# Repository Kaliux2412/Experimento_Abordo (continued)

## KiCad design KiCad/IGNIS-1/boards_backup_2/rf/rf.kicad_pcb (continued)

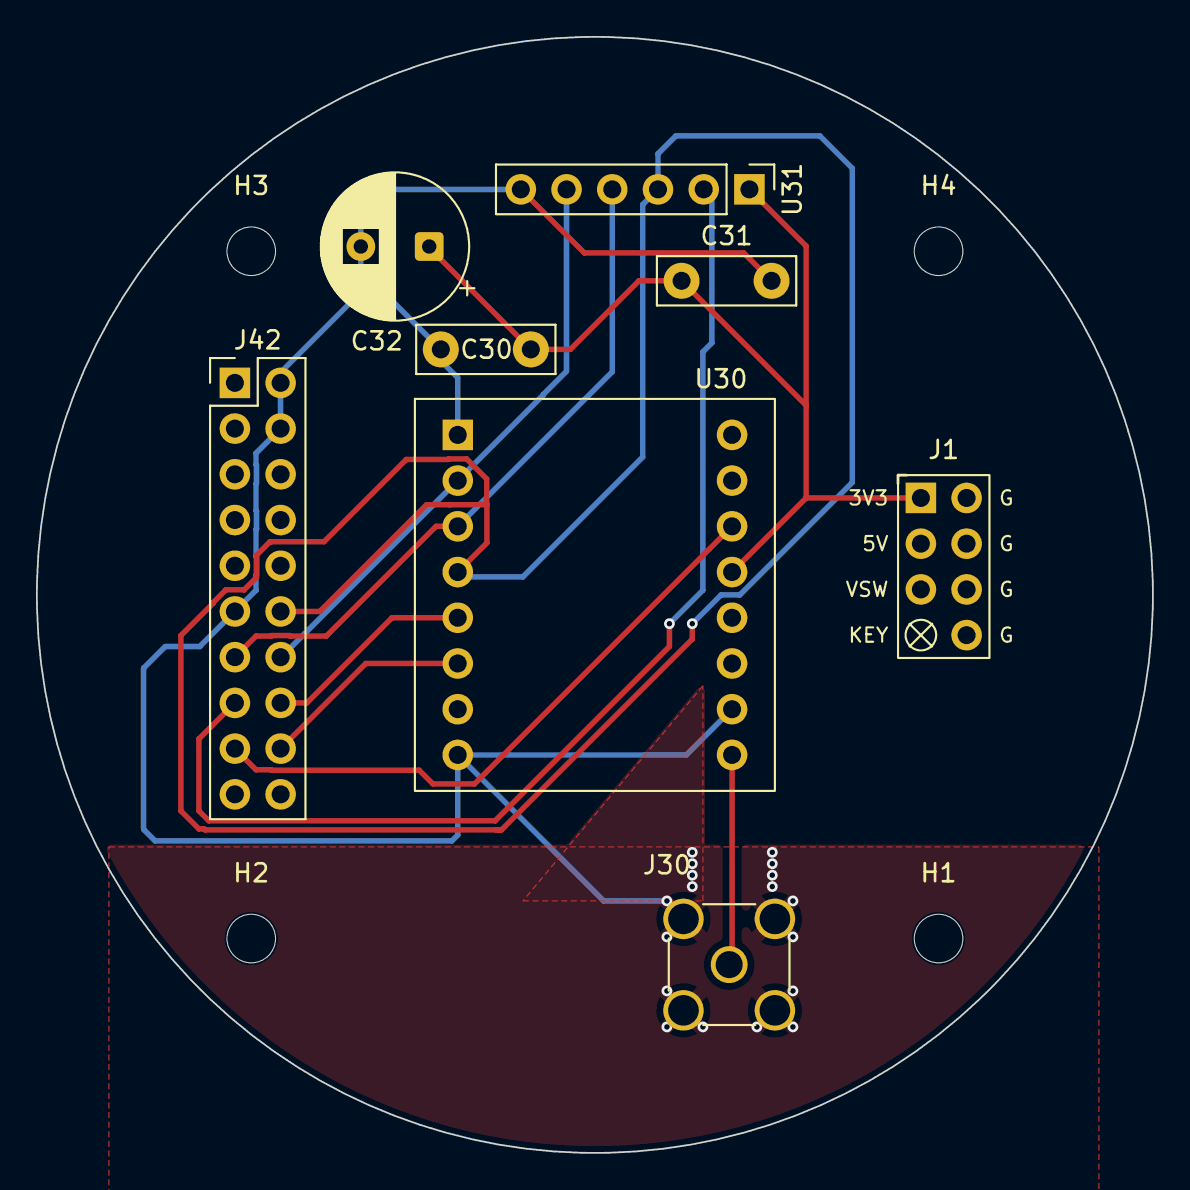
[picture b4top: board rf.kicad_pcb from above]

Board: 2 copper layers, 62.0 x 62.0 mm, 12 parts (0 on the bottom side), 10 nets.

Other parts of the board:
H1, H2, H3, H4: M2.5_hole; MountingHole_2.7mm_M2.5

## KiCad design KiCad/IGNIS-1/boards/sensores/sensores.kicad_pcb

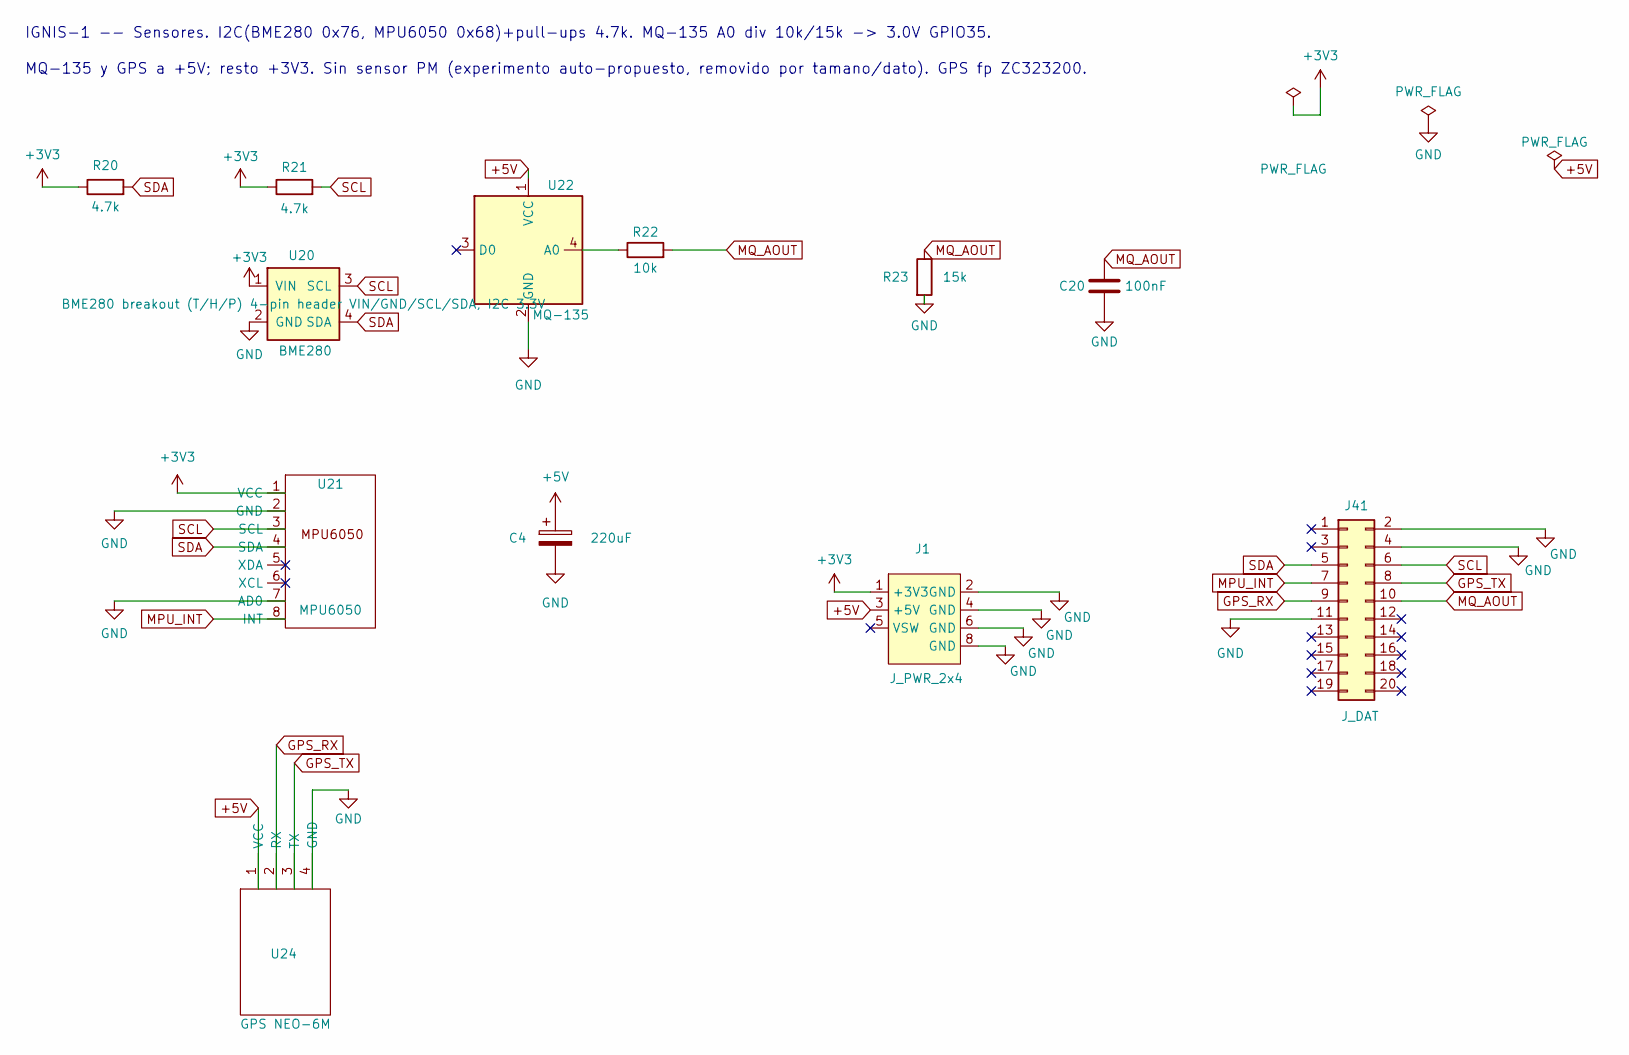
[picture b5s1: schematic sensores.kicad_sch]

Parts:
C4: 220uF; CP_Radial_D13.0mm_P5.00mm
C20: 100nF; C_Disc_D7.5mm_W2.5mm_P5.00mm
J1: J_PWR_2x4; J_PWR_2x4_Keyed
J41: J_DAT; PinHeader_2x10_P2.54mm_Vertical
R20, R21: 4.7k; R_Axial_DIN0207_L6.3mm_D2.5mm_P7.62mm_Horizontal
R22: 10k; R_Axial_DIN0207_L6.3mm_D2.5mm_P7.62mm_Horizontal
R23: 15k; R_Axial_DIN0207_L6.3mm_D2.5mm_P7.62mm_Horizontal
U20: BME280; PinHeader_1x04_P2.54mm_Vertical
U21: MPU6050; MPU6050_module
U22: MQ-135; PinHeader_1x04_P2.54mm_Vertical
U24: GPS NEO-6M; GPS_NEO6M_module

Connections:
+3V3: J1.1 (+3V3), R20.1, R21.1, U20.1 (VIN), U21.1 (VCC)
+5V: C4.1, J1.3 (+5V), U22.1 (VCC), U24.1 (VCC)
GND: C4.2, C20.2, J1.2 (GND), J1.4 (GND), J1.6 (GND), J1.8 (GND), J41.2, J41.4, J41.11, R23.2, U20.2 (GND), U21.2 (GND), U21.7 (AD0), U22.2 (GND), U24.4 (GND)
GPS_RX: J41.9, U24.2 (RX)
GPS_TX: J41.8, U24.3 (TX)
MPU_INT: J41.7, U21.8 (INT)
MQ_AOUT: C20.1, J41.10, R22.2, R23.1
unnamed: R22.1, U22.4 (A0)
SCL: J41.6, R21.2, U20.3 (SCL), U21.3 (SCL)
SDA: J41.5, R20.2, U20.4 (SDA), U21.4 (SDA)

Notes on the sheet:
IGNIS-1 -- Sensores. I2C(BME280 0x76, MPU6050 0x68)+pull-ups 4.7k. MQ-135 A0 div 10k/15k -> 3.0V GPIO35.
MQ-135 y GPS a +5V; resto +3V3. Sin sensor PM (experimento auto-propuesto, removido por tamano/dato). GPS fp ZC323200.

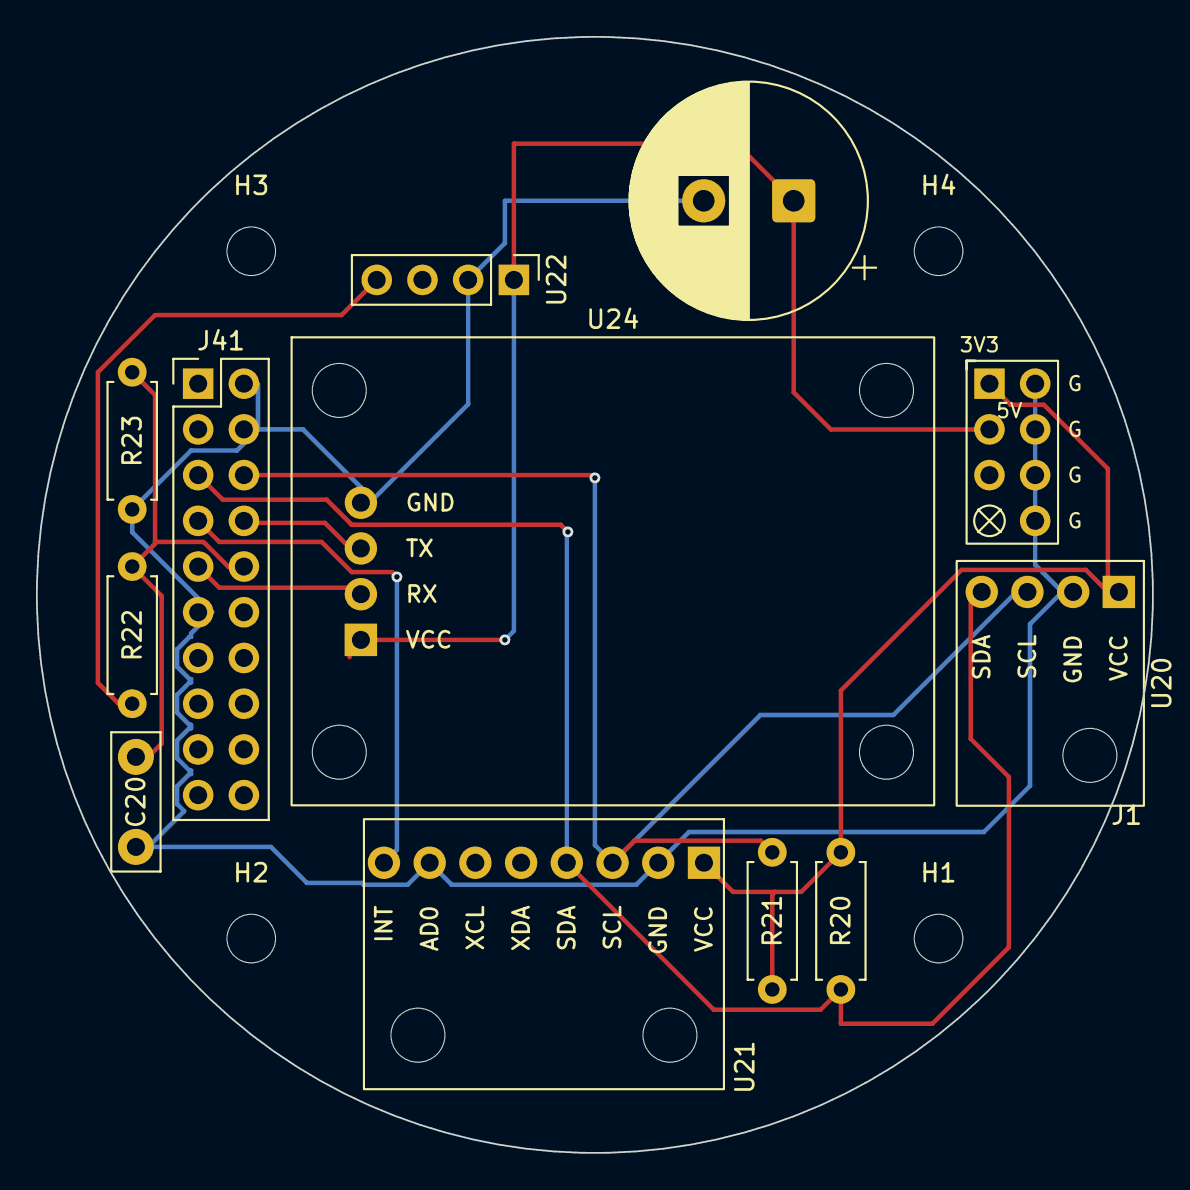
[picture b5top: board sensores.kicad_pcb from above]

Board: 2 copper layers, 62.0 x 62.0 mm, 16 parts (0 on the bottom side), 10 nets.

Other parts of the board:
H1, H2, H3, H4: M2.5_hole; MountingHole_2.7mm_M2.5

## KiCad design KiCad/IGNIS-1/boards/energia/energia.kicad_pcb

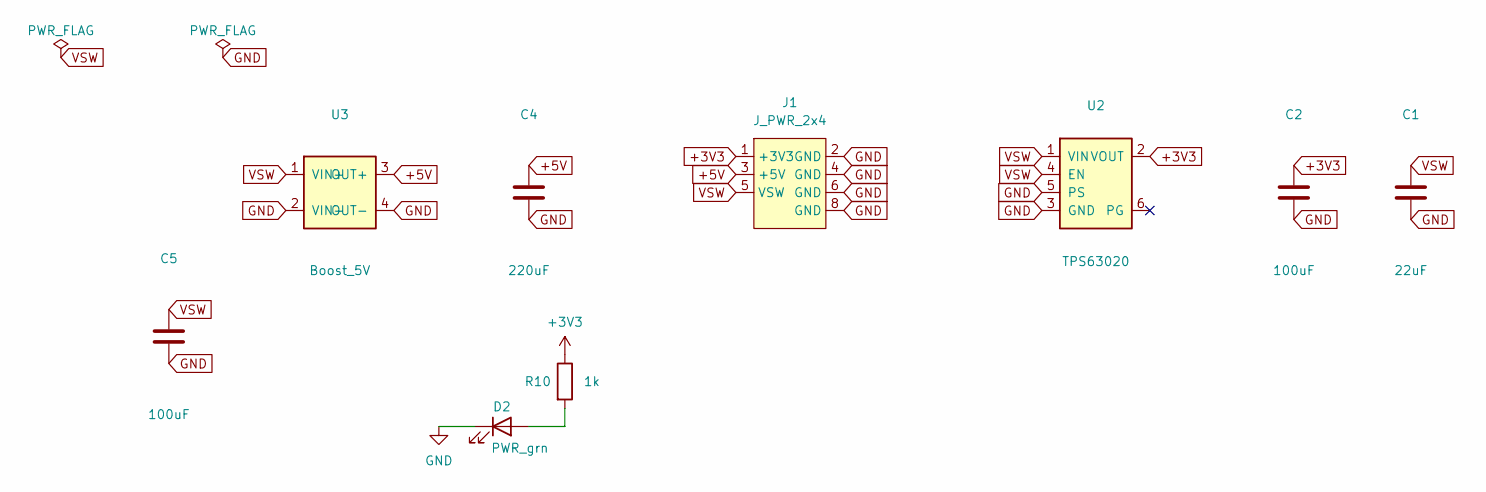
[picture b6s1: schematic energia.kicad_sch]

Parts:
C1: 22uF; CP_Radial_D6.3mm_P2.50mm
C2, C5: 100uF; CP_Radial_D8.0mm_P3.80mm
C4: 220uF; CP_Radial_D13.0mm_P5.00mm
D2: PWR_grn; LED_D3.0mm
J1: J_PWR_2x4; J_PWR_2x4_Keyed
R10: 1k; R_Axial_DIN0207_L6.3mm_D2.5mm_P7.62mm_Horizontal
U2: TPS63020; TPS63020_module
U3: Boost_5V; MT3608_module

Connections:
+3V3: C2.1, J1.1 (+3V3), R10.1, U2.2 (VOUT)
+5V: C4.1, J1.3 (+5V), U3.3 (OUT+)
GND: C1.2, C2.2, C4.2, C5.2, D2.1 (K), J1.2 (GND), J1.4 (GND), J1.6 (GND), J1.8 (GND), U2.3 (GND), U2.5 (PS), U3.2 (VIN-), U3.4 (OUT-)
unnamed: D2.2 (A), R10.2
VSW: C1.1, C5.1, J1.5 (VSW), U2.1 (VIN), U2.4 (EN), U3.1 (VIN+)

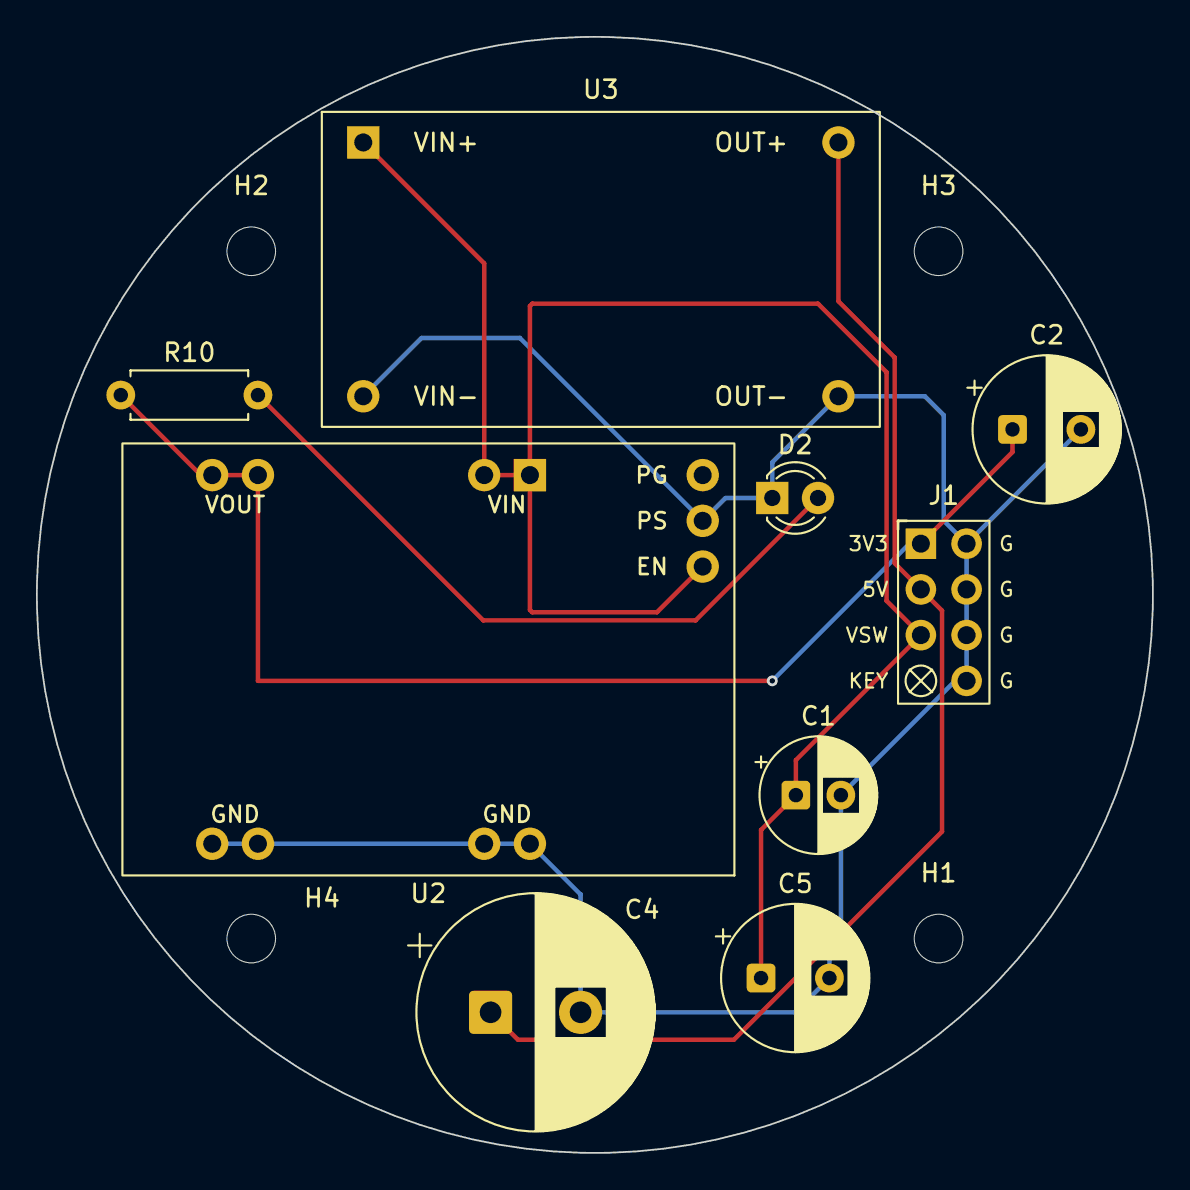
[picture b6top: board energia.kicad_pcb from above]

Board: 2 copper layers, 62.0 x 62.0 mm, 13 parts (0 on the bottom side), 5 nets.

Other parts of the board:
H1, H2, H3, H4: M2.5_hole; MountingHole_2.7mm_M2.5

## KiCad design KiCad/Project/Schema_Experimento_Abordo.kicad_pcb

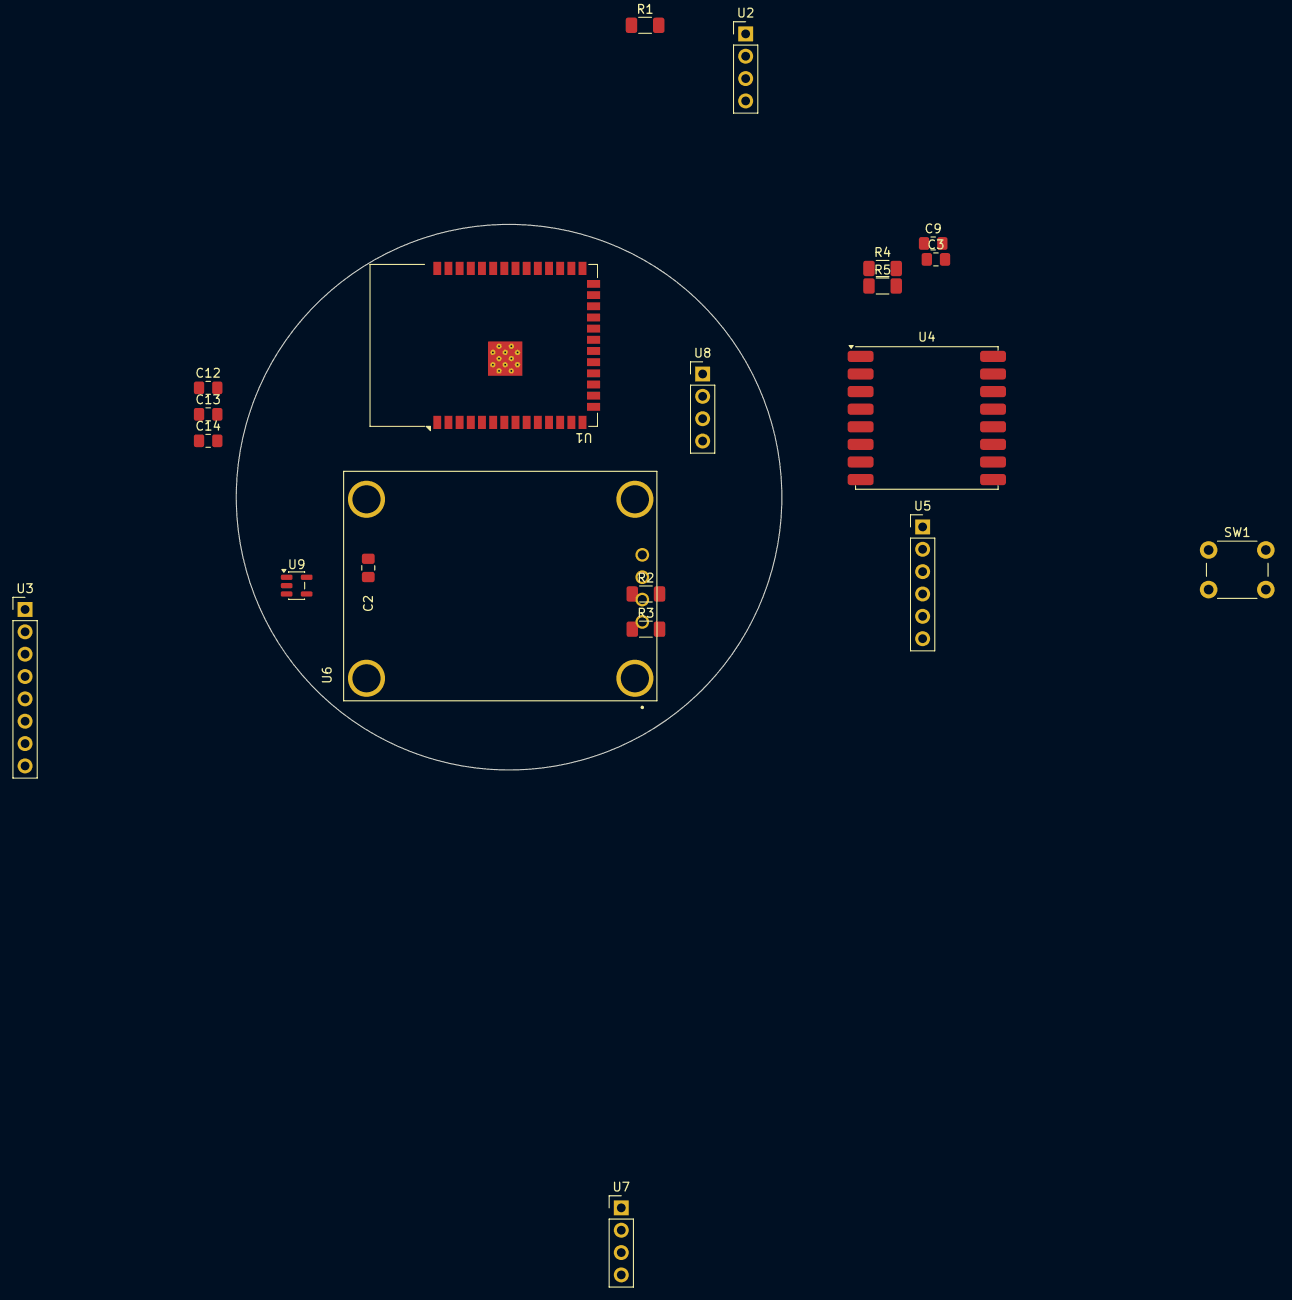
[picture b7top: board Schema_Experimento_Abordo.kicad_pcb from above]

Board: 2 copper layers, 62.0 x 62.0 mm, 21 parts (0 on the bottom side), 17 nets, no tracks yet.

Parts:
C2, C9, C12, C13: 10uF; C_0805_2012Metric_Pad1.18x1.45mm_HandSolder
C3: 0.1uF; C_0805_2012Metric_Pad1.18x1.45mm_HandSolder
C14: 100nF; C_0805_2012Metric_Pad1.18x1.45mm_HandSolder
R1: 10k; R_1206_3216Metric_Pad1.30x1.75mm_HandSolder
R2, R3: 4.7k; R_1206_3216Metric_Pad1.30x1.75mm_HandSolder
R4, R5: 100k; R_1206_3216Metric_Pad1.30x1.75mm_HandSolder
SW1: RESET; SW_PUSH_6mm_H4.3mm
U1: ESP32-S3-WROOM-1
U2: BME280; PinHeader_1x04_P2.54mm_Vertical
U3: PinHeader_1x08_P2.54mm_Vertical
U4: HOPERF_RFM9XW_SMD
U5: Micro_SD; PinHeader_1x06_P2.54mm_Vertical
U6: ZC323200; XCVR_ZC323200
U7: SGP30; PinHeader_1x04_P2.54mm_Vertical
U8: PinHeader_1x04_P2.54mm_Vertical
U9: AP2112K-3.3; SOT-23-5

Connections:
+3.3V: C2.1, C9.1, C13.1, C14.1, R1.2, R2.2, R3.2, U1.1 (3V3), U1.16 (VIN), U2.1 (VIN), U3.1 (VCC), U4.12 (3.3V), U5.1 (VCC), U6.1 (VCC), U7.1 (VIN), U8.1 (VIN), U9.5 (VOUT)
+BATT: C12.1, R5.1, U9.1 (VIN), U9.3 (EN)
/CS MicroSD: U1.18 (D13), U5.2 (CS)
/DIO0 LoRa: U1.22 (D26), U4.11 (DIO0)
/GPS_RX: U1.7 (TX2), U6.2 (RX)
/GPS_TX: U1.6 (RX2), U6.3 (TX)
/MISO SPI: U1.10 (D19), U4.2 (MISO), U5.5 (MISO)
/MOSI SPI: U1.15 (D23), U4.3 (MOSI), U5.3 (MOSI)
/MPU6050 INT: U1.21 (D27), U3.8 (INT)
/NSS LoRa: U1.8 (D5), U4.5 (NSS)
/RST LoRa: U1.20 (D14), U4.6 (RESET)
/SCK SPI: U1.9 (D18), U4.4 (SCK), U5.4 (CLK)
/SCL: R3.1, U1.25 (D32), U2.3 (SCL), U3.3 (SCL), U7.3 (SCL), U8.3 (SCL)
/SDA: R2.1, U1.24 (D33), U2.4 (SDA), U3.4 (SDA), U7.4 (SDA), U8.4 (SDA)
GND: C2.2, C3.2, C9.2, C12.2, C13.2, C14.2, R4.1, SW1.1, U1.2 (GND), U1.17 (GND), U1.40 (GND), U1.41 (GND), U2.2 (GND), U3.2 (GND), U3.7 (AD0), U4.1 (GND), U5.6 (GND), U6.4 (GND), U6.SH1 (GND), U6.SH2 (GND), U6.SH3 (GND), U6.SH4 (GND), U7.2 (GND), U8.2 (GND), U9.2 (GND)
unnamed: R4.2, R5.2, U1.27 (D34)
unnamed: C3.1, R1.1, SW1.2, U1.30 (EN)

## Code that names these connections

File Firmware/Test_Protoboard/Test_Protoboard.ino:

/*
 * IGNIS-1 — Test de protoboard (bring-up de hardware)
 * --------------------------------------------------------------
 * NO es el firmware de vuelo. Solo verifica que cada periferico
 * responde, con el pin-map del diseno. Cada subsistema imprime
 * PASS/FAIL y se puede desactivar si el modulo no esta conectado.
 *
 * Pin-map (ESP32 DevKit 38p):
 *   I2C  SDA/SCL ......... 33 / 32   (BME280 0x76, MPU6050 0x68)
 *   SPI  SCK/MISO/MOSI ... 18 / 19 / 23   (LoRa + microSD, CS separados)
 *   LoRa CS/RST/DIO0 ..... 5 / 14 / 26   (RFM95W 433 MHz)
 *   microSD CS ........... 13
 *   MPU_INT .............. 27
 *   Buzzer ............... 25   (activo)
 *   LED status ........... 4
 *   GPS  RX2/TX2 ......... 16 / 17   (NEO-6M, 9600 baud)
 *   MQ-135 A0 ............ 35   (ADC1, via divisor 10k/15k)
 *
 * Librerias (Library Manager):
 *   Adafruit BME280, Adafruit MPU6050, Adafruit Unified Sensor,
 *   TinyGPSPlus, LoRa (Sandeep Mistry), SD (incluida).
 *
 * Notas:
 *   - MQ-135 necesita calentamiento (varios minutos); valores
 *     inestables al inicio. El divisor 10k/15k baja A0 (0-5V) a ~0-3V.
 *   - Alimentar MQ-135 y GPS a 5V; ESP/sensores I2C a 3.3V.
 */

#include <Wire.h>
#include <SPI.h>
#include <Adafruit_Sensor.h>
#include <Adafruit_BME280.h>
#include <Adafruit_MPU6050.h>
#include <TinyGPSPlus.h>
#include <SD.h>
#include <LoRa.h>

// ---------- activar/desactivar pruebas ----------
#define TEST_BME280   1
#define TEST_MPU6050  1
#define TEST_MQ135    1
#define TEST_GPS      1
#define TEST_SD       0   // sin modulo microSD (no comprado aun)
#define TEST_LORA     0   // sin modulo RFM95W (no comprado aun)

// ---------- pines ----------
#define I2C_SDA   33
#define I2C_SCL   32
#define SPI_SCK   18
#define SPI_MISO  19
#define SPI_MOSI  23
#define LORA_CS    5
#define LORA_RST  14
#define LORA_DIO0 26
#define SD_CS     13
#define MPU_INT   27
#define BUZZER    25
#define LED       4
#define GPS_RX    16    // ESP RX2 <- GPS TX
#define GPS_TX    17    // ESP TX2 -> GPS RX
#define MQ_AOUT   35    // ADC1 (input-only)
#define LORA_FREQ 433E6

// divisor MQ-135: A0 --[10k]--+--[15k]-- GND ; tap = ADC
const float MQ_DIV = (10.0 + 15.0) / 15.0;   // factor inverso = 1.667

Adafruit_BME280 bme;
Adafruit_MPU6050 mpu;
TinyGPSPlus gps;

bool okBME=false, okMPU=false, okSD=false, okLoRa=false;
uint32_t seq=0;

// ---------- offsets de calibracion MPU6050 ----------
// Se calculan en reposo al boot. Accel: se asume placa plana, Z arriba
// (az debe quedar ~9.81 m/s2, ax/ay ~0). Gyro: los tres ejes ~0 rad/s.
const float G0 = 9.80665;          // gravedad estandar (m/s2)
float axOff=0, ayOff=0, azOff=0;   // bias accel (m/s2)
float gxOff=0, gyOff=0, gzOff=0;   // bias gyro (rad/s)

void beep(int ms){ digitalWrite(BUZZER,HIGH); delay(ms); digitalWrite(BUZZER,LOW); }
void line(){ Serial.println(F("------------------------------------------")); }

void i2cScan(){
  Serial.println(F("[I2C] scan:"));
  int n=0;
  for(uint8_t a=1;a<127;a++){
    Wire.beginTransmission(a);
    if(Wire.endTransmission()==0){
      Serial.printf("   0x%02X", a);
      if(a==0x76||a==0x77) Serial.print(F(" (BME280)"));
      if(a==0x68||a==0x69) Serial.print(F(" (MPU6050)"));
      Serial.println();
      n++;
    }
  }
  Serial.printf("   %d dispositivo(s)\n", n);
}

#if TEST_MPU6050
// Promedia N muestras en reposo y calcula los offsets.
// IMPORTANTE: la placa debe estar quieta y plana durante la calibracion.
void calibrarMPU(int n=1000){
  Serial.printf("[MPU6050] calibrando (%d muestras, no mover)...\n", n);
  double sax=0,say=0,saz=0, sgx=0,sgy=0,sgz=0;
  sensors_event_t a,g,tmp;
  for(int i=0;i<n;i++){
    mpu.getEvent(&a,&g,&tmp);
    sax+=a.acceleration.x; say+=a.acceleration.y; saz+=a.acceleration.z;
    sgx+=g.gyro.x;         sgy+=g.gyro.y;         sgz+=g.gyro.z;
    delay(2);
  }
  axOff = sax/n;           // en reposo plano ax~0 -> todo es bias
  ayOff = say/n;           // ay~0 -> todo es bias
  azOff = saz/n - G0;      // az debe ser G0; el exceso es bias
  gxOff = sgx/n;           // gyro en reposo ~0 -> todo es bias
  gyOff = sgy/n;
  gzOff = sgz/n;
  Serial.printf("[MPU6050] offset accel: ax=%.3f ay=%.3f az=%.3f m/s2\n", axOff, ayOff, azOff);
  Serial.printf("[MPU6050] offset gyro:  gx=%.4f gy=%.4f gz=%.4f rad/s\n", gxOff, gyOff, gzOff);
}
#endif

void setup(){
  Serial.begin(115200);
  delay(500);
  pinMode(LED, OUTPUT);
  pinMode(BUZZER, OUTPUT);
  pinMode(MPU_INT, INPUT);
  digitalWrite(LED,HIGH); beep(120); digitalWrite(LED,LOW);

  line();
  Serial.println(F("IGNIS-1 — Test de protoboard"));
  line();

  Wire.begin(I2C_SDA, I2C_SCL);
  i2cScan();

#if TEST_BME280
  okBME = bme.begin(0x76) || bme.begin(0x77);
  Serial.printf("[BME280]  %s\n", okBME ? "PASS" : "FAIL (revisar I2C/dir)");
#endif

#if TEST_MPU6050
  okMPU = mpu.begin(0x68);
  if(okMPU){
    mpu.setAccelerometerRange(MPU6050_RANGE_8_G);
    mpu.setGyroRange(MPU6050_RANGE_500_DEG);
    mpu.setFilterBandwidth(MPU6050_BAND_21_HZ);   // filtra ruido antes de calibrar
  }
  Serial.printf("[MPU6050] %s\n", okMPU ? "PASS" : "FAIL");
  if(okMPU) calibrarMPU();
#endif

#if TEST_MQ135
  analogReadResolution(12);
  analogSetPinAttenuation(MQ_AOUT, ADC_11db);   // rango ~0-3.1V
  Serial.println(F("[MQ-135]  ADC listo (necesita warmup)"));
#endif

#if TEST_GPS
  Serial2.begin(9600, SERIAL_8N1, GPS_RX, GPS_TX);
  Serial.println(F("[GPS]     UART2 abierto (esperando NMEA)"));
#endif

#if (TEST_SD || TEST_LORA)
  SPI.begin(SPI_SCK, SPI_MISO, SPI_MOSI);
#endif

#if TEST_SD
  okSD = SD.begin(SD_CS, SPI);
  Serial.printf("[microSD] %s\n", okSD ? "PASS" : "FAIL");
  if(okSD){
    File f = SD.open("/test.txt", FILE_APPEND);
    if(f){ f.println("IGNIS-1 test boot"); f.close(); Serial.println(F("   escribio /test.txt")); }
  }
#endif

#if TEST_LORA
  LoRa.setPins(LORA_CS, LORA_RST, LORA_DIO0);
  okLoRa = LoRa.begin(LORA_FREQ);
  if(okLoRa) LoRa.setSyncWord(0x12);
  Serial.printf("[LoRa]    %s (433 MHz)\n", okLoRa ? "PASS" : "FAIL");
#endif

  line();
  Serial.println(F("Loop: lecturas cada 2 s"));
  line();
  if(okBME && okMPU){ beep(60); delay(60); beep(60); }  // doble beep = sensores I2C OK
}

void loop(){
  digitalWrite(LED, !digitalRead(LED));   // latido

  // alimentar parser GPS continuamente
#if TEST_GPS
  while(Serial2.available()) gps.encode(Serial2.read());
#endif

  Serial.println();

#if TEST_BME280
  if(okBME){
    Serial.printf("BME280:  T=%.2f C  RH=%.1f %%  P=%.1f hPa\n",
                  bme.readTemperature(), bme.readHumidity(), bme.readPressure()/100.0);
  }
#endif

#if TEST_MPU6050
  if(okMPU){
    sensors_event_t a,g,tmp; mpu.getEvent(&a,&g,&tmp);
    // resta offsets: accel debe dar ~0/0/9.81 en reposo, gyro ~0/0/0
    float ax=a.acceleration.x-axOff, ay=a.acceleration.y-ayOff, az=a.acceleration.z-azOff;
    float gx=g.gyro.x-gxOff, gy=g.gyro.y-gyOff, gz=g.gyro.z-gzOff;
    Serial.printf("MPU6050: ax=%.2f ay=%.2f az=%.2f m/s2 | gx=%.3f gy=%.3f gz=%.3f rad/s\n",
                  ax, ay, az, gx, gy, gz);
  }
#endif

#if TEST_MQ135
  {
    int mv = analogReadMilliVolts(MQ_AOUT);     // mV en el ADC (tras divisor)
    float a0 = mv/1000.0 * MQ_DIV;              // V reales en A0 del modulo
    Serial.printf("MQ-135:  ADC=%d mV  A0~=%.2f V  (warmup necesario)\n", mv, a0);
  }
#endif

#if TEST_GPS
  if(gps.location.isValid()){
    Serial.printf("GPS:     %.6f, %.6f  sats=%d  alt=%.1f m\n",
                  gps.location.lat(), gps.location.lng(),
                  gps.satellites.value(), gps.altitude.meters());
  } else {
    Serial.printf("GPS:     sin fix (chars=%lu, sats=%d)\n",
                  (unsigned long)gps.charsProcessed(), gps.satellites.value());
  }
#endif

#if TEST_LORA
  if(okLoRa){
    LoRa.beginPacket();
    LoRa.printf("IGNIS-1 test seq=%lu", (unsigned long)seq);
    LoRa.endPacket();
    Serial.printf("LoRa:    TX seq=%lu\n", (unsigned long)seq);
    seq++;
  }
#endif

  delay(2000);
}

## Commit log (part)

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2026-06-21 Create Project
2026-06-21 Add .gitkeep file to Project directory
2026-06-21 Add .gitkeep to Libraries&Components directory
2026-06-21 Se agrego Componente ZC323200
2026-06-21 Actualizacion PCB
2026-06-22 Se agregó Schema modificado de otro repo. Se agregó PCB generado con ese Schema.
2026-06-22 Primer reporte ERC - revisar errores
2026-06-23 Esquematico limpio y probado. PCB Actualizado. Falta definir si se cambia el U9 por un Buck-boost
2026-06-23 Agregado SGP30
2026-06-24 Board Cerebro - Initial Commit
2026-06-24 PCB del MCU creado
2026-06-24 PCB de RF - Initial Commit
2026-06-24 PCB Sensores - Initial Commit
2026-06-24 Initial Commit del project IGNIS
2026-06-24 IGNIS librerias inciales
2026-06-24 Pines corregidos en ESP32
2026-06-25 Schematic arreglado. Footprint del ESP32 ajustado.
2026-06-26 Tracks listos en PCB
2026-06-27 Placa 5 (Sensores)
2026-06-28 Placa 2 GPS
2026-06-28 Placa 3 (ESP32)
2026-06-30 Tipo .SVG listos
2026-06-30 Tipo .svg Formato Correcto
2026-06-30 Se agregaron los Firmwares iniciales
2026-06-30 Actualizado los boards de IGNIS - separado en 3 boards
2026-06-30 Agregada documentacion de soporte
